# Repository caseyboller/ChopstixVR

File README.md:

A prototype I made in 2020 for a haptic chopstick to be used in VR, developed from PCB to Unity/Arduino.

[Design](https://github.com/caseyboller/ChopstixVR/assets/36660680/1214c257-8176-43c2-80a8-be5d32b23608)

[CAD design](https://github.com/caseyboller/ChopstixVR/assets/36660680/7751c19b-aa32-42bb-81e6-dfa4c7f0dddc)

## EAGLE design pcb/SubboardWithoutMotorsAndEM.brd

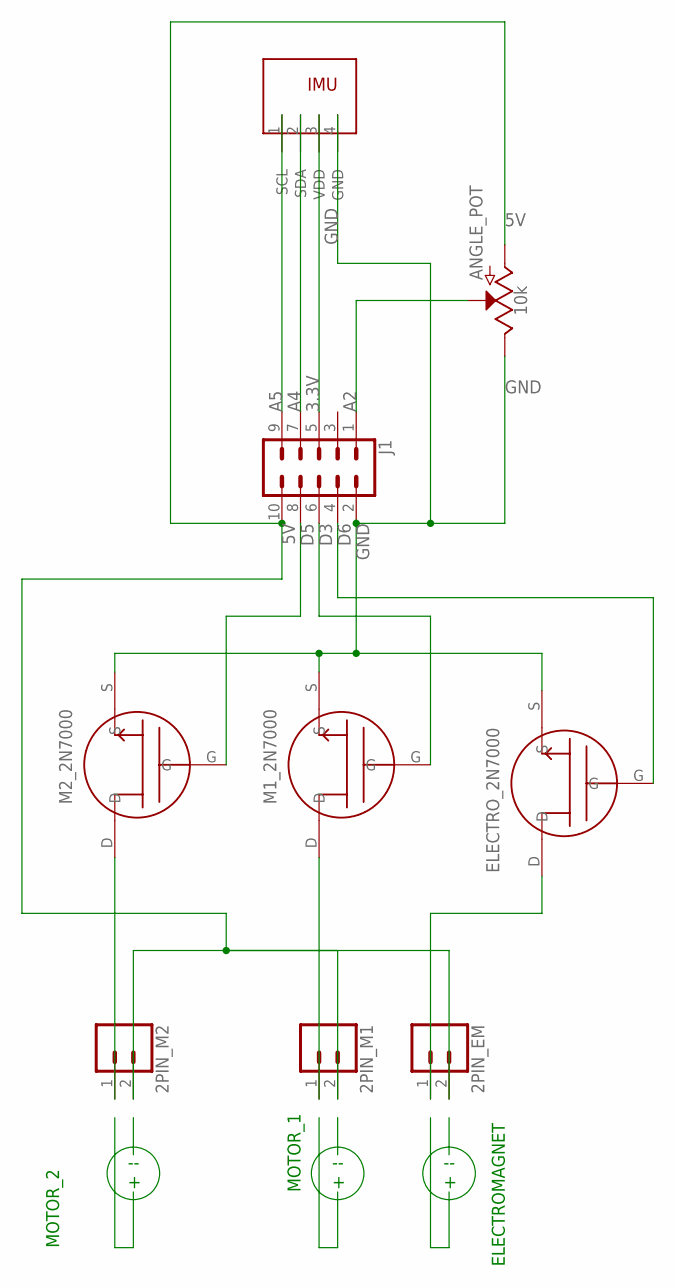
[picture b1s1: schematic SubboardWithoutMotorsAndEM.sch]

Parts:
2PIN_EM, 2PIN_M1, 2PIN_M2: CONN_02; 1X02
ANGLE_POT: 10k; POT-PTH-ALPS-KIT
ELECTRO_2N7000: 2N7000_N_FET
J1: CONN_05X2SHD; 2X5-SHROUDED
M1_2N7000, M2_2N7000: 2N7000_N_FET
U$1: MPU-9250

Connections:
3.3V: J1.5, U$1.3 (VDD)
5V: 2PIN_EM.2, 2PIN_M1.2, 2PIN_M2.2, ANGLE_POT.P$3 (A), J1.10
A2: ANGLE_POT.P$2 (S), J1.1
A4: J1.7, U$1.2 (SDA)
A5: J1.9, U$1.1 (SCL)
D3: J1.6, M1_2N7000.G
D5: J1.8, M2_2N7000.G
D6: ELECTRO_2N7000.G, J1.4
GND: ANGLE_POT.P$1 (E), ELECTRO_2N7000.S, J1.2, M1_2N7000.S, M2_2N7000.S, U$1.4 (GND)
unnamed: 2PIN_M2.1, M2_2N7000.D
unnamed: 2PIN_M1.1, M1_2N7000.D
unnamed: 2PIN_EM.1, ELECTRO_2N7000.D

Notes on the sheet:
MOTOR_2
MOTOR_1
ELECTROMAGNET
-- +

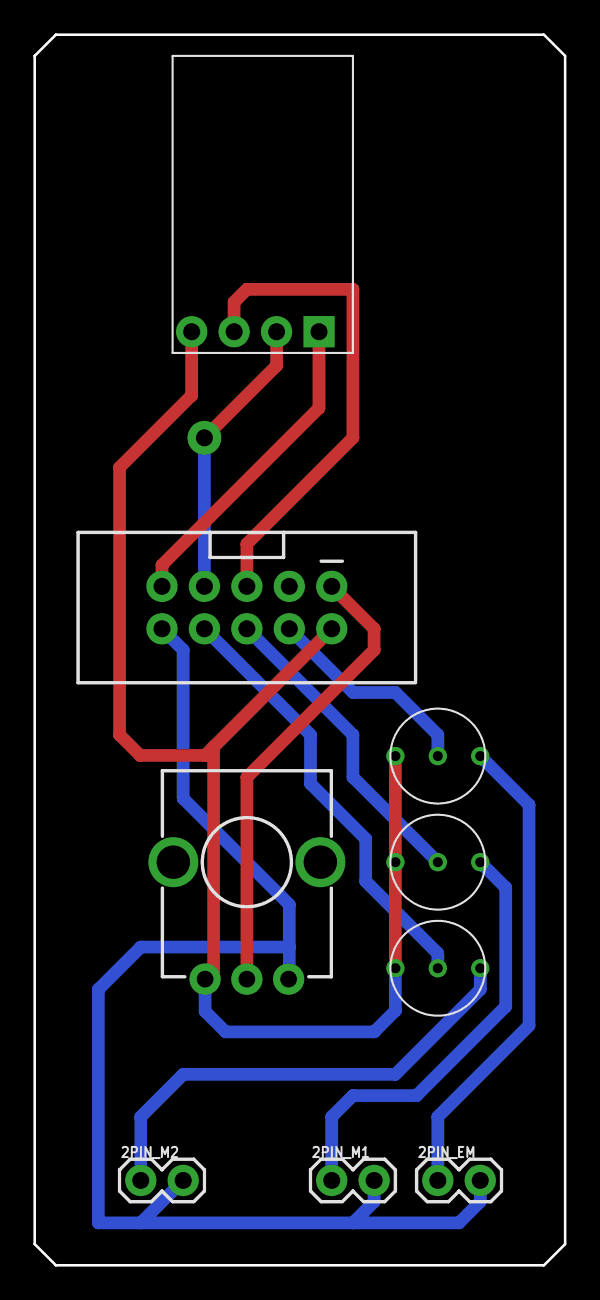
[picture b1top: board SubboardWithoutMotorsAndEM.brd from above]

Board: 2 copper layers, 31.7 x 73.7 mm, 9 parts (0 on the bottom side), 12 nets.

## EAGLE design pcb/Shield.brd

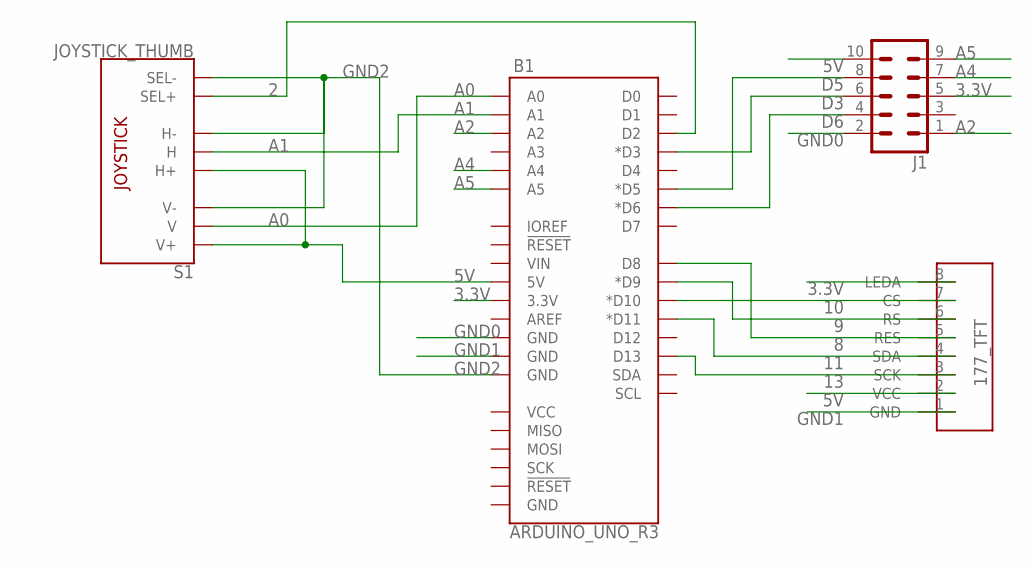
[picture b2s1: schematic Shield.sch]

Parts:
1.77_TFT: TFT_DISPL_1.77"; TFT_DISP
B1: ARDUINO_UNO_R3; ARDUINO_R3
J1: CONN_05X2SHD; 2X5-SHROUDED
S1: JOYSTICK_THUMB; JOYSTICK

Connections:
2: B1.D2, S1.B1A (SEL+)
3.3V: 1.77_TFT.8 (LEDA), B1.3.3V, J1.5
5V: 1.77_TFT.2 (VCC), B1.5V, J1.10, S1.H1 (H+), S1.V1 (V+)
8: 1.77_TFT.5 (RES), B1.D8
9: 1.77_TFT.6 (RS), B1.D9 (*D9)
10: 1.77_TFT.7 (CS), B1.D10 (*D10)
11: 1.77_TFT.4 (SDA), B1.D11 (*D11)
13: 1.77_TFT.3 (SCK), B1.D13
A0: B1.A0, S1.V2 (V)
A1: B1.A1, S1.H2 (H)
A2: B1.A2, J1.1
A4: B1.A4, J1.7
A5: B1.A5, J1.9
D3: B1.D3 (*D3), J1.6
D5: B1.D5 (*D5), J1.8
D6: B1.D6 (*D6), J1.4
GND0: B1.GND@4 (GND), J1.2
GND1: 1.77_TFT.1 (GND), B1.GND@3 (GND)
GND2: B1.GND@2 (GND), S1.B2A (SEL-), S1.H3 (H-), S1.V3 (V-)

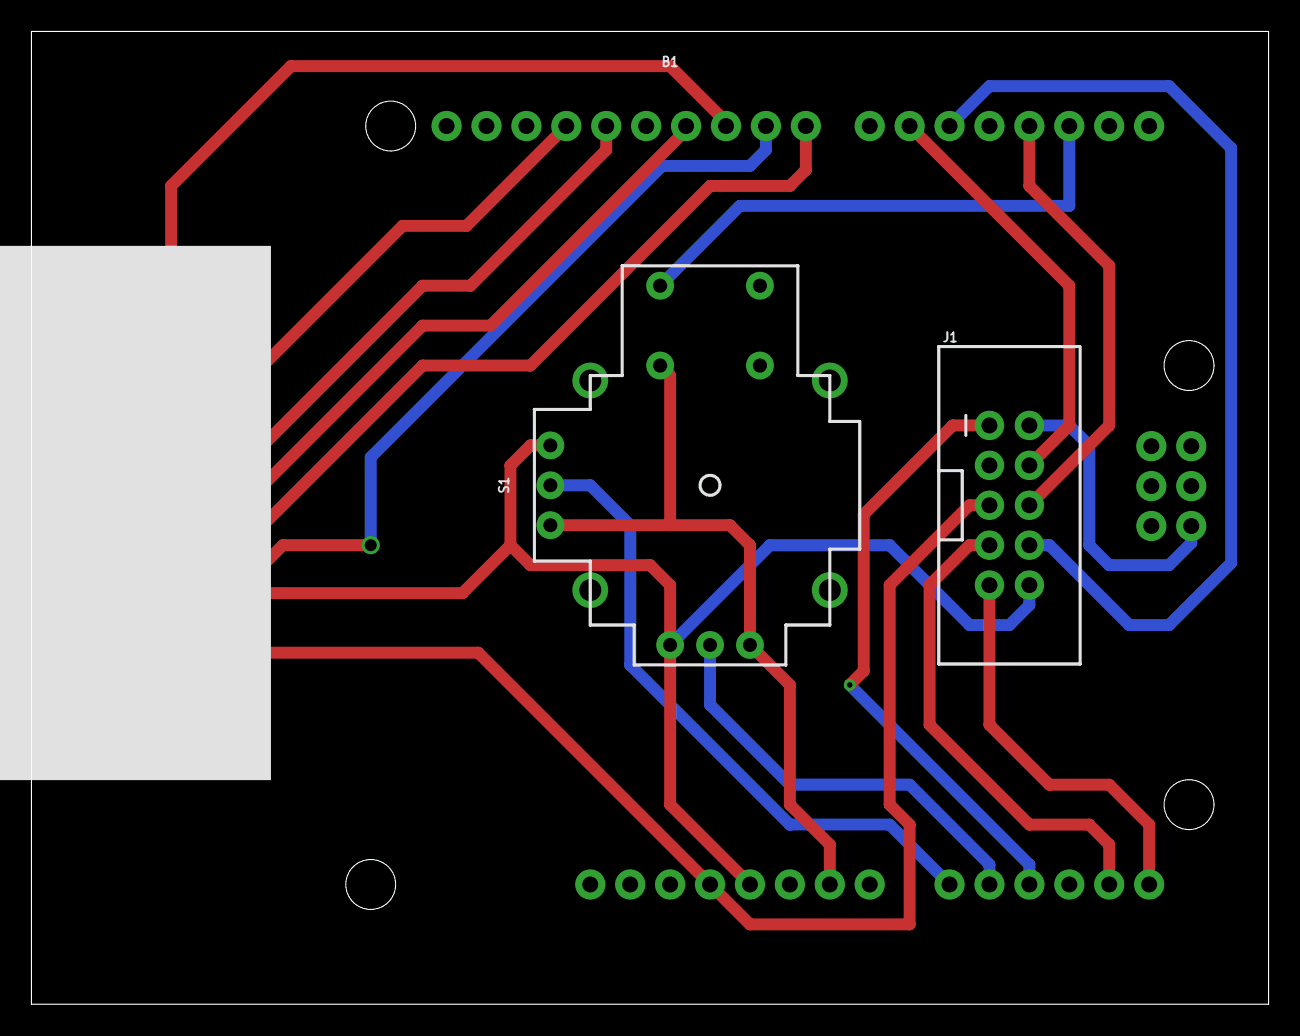
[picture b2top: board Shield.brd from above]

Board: 2 copper layers, 78.7 x 61.9 mm, 4 parts (0 on the bottom side), 19 nets.

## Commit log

2024-06-18 Add submitted project files from 2020

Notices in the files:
parts and their libraries:
SparkFun-Boards: Licensing: Creative Commons ShareAlike 4.0 International - https://creativecommons.org/licenses/by-sa/4.0
